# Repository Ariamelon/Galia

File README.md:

# Galia
USB-C breakout board.

## Disclaimer
This board is licensed under CC BY 4.0.
## Key Features
* Full ESD protection for data lines and VBUS.
* Two buttons on board that can be snapped off.
* Two M3 mounting holes, one of which is connected to ground for earthing the chassis.
* 6-pin JST SH connector capable of handling up to 3A power.

## Changelog
* 26/07/2023: Fixed position of button and mounting holes. Added JLC tooling holes.
* 25/07/2023: Changed 8 pin JST SH connector to 6 pin. Changed orientation of SH connectors for easier routing of wires. Added Ariamelon logo. Added PCB cutouts to allow for buttons to be snapped off.
* 21/07/2023: Changed 20 pin FFC to 7 pin and 8 pin JST SH connector. Fixed orientation.
* 18/07/2023: Changed JST connector back to 20 pin FFC. Centered connector.
* 17/07/2023: Changed 20 pin FFC connector to 14 pin JST SH connector. Repositioned components.
* 16/07/2023: Changed PTS645 LCSC part number.
* 14/07/2023: Initial public upload of V1.0.

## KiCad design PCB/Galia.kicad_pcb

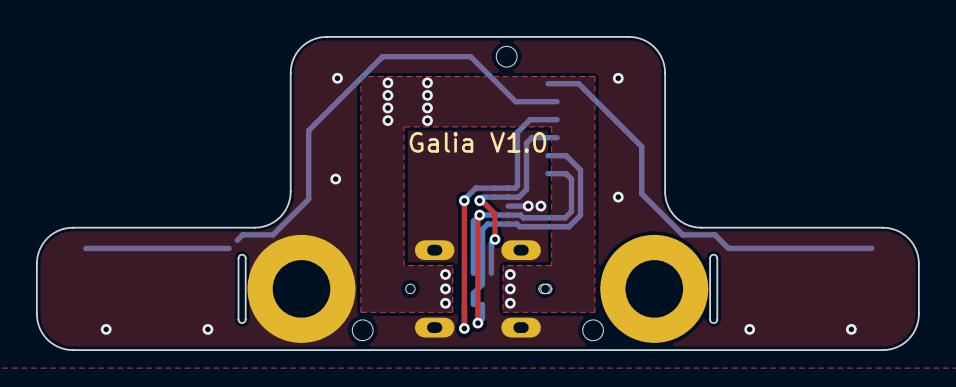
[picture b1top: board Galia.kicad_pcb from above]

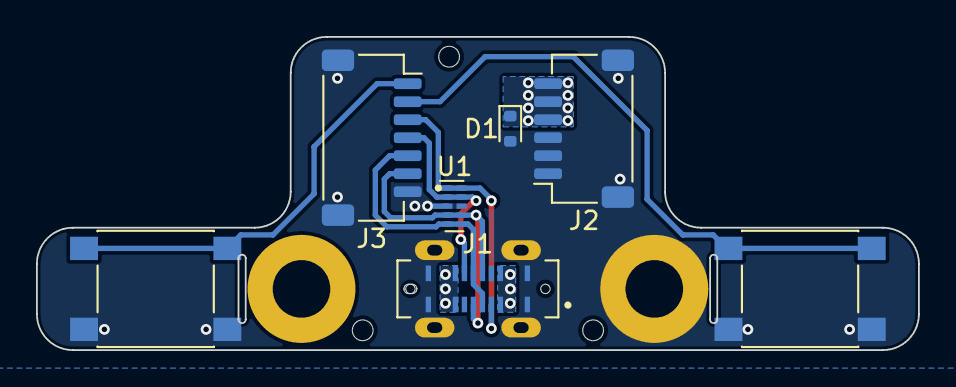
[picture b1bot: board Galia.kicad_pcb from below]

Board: 2 copper layers, 49.0 x 17.4 mm, 13 parts (9 on the bottom side), 8 nets.

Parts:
A1: Ariamelon Logo; Ariamelon_Logo_Mask
D1: 5V; D_SOD-523
H1, H2: M3; MountingHole_3.2mm_M3_Pad
H3, H4, H5: Tooling Hole; JLC Tooling Hole
J1: USB In; CON-USB4120-03-C-REVA
J2: Power; JST_SH_SM06B-SRSS-TB_1x06-1MP_P1.00mm_Horizontal
J3: I/O; JST_SH_SM07B-SRSS-TB_1x07-1MP_P1.00mm_Horizontal
SW1, SW2: PTS645; SW_SPST_PTS645
U1: TPD4E05U06; USON-10_2.5x1.0mm_P0.5mm

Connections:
/BOOTSEL: J3.1, SW2.2 (B)
/D+: J1.A6 (D+), J1.B6 (D+), J3.5, U1.5 (IO4), U1.6 (NC)
/D-: J1.A7 (D-), J1.B7 (D-), J3.6, U1.4 (IO3), U1.7 (NC)
/~RST: J3.2, SW1.2 (B)
CC1: J1.A5 (CC1), J3.3, U1.1 (IO1), U1.10 (NC)
CC2: J1.B5 (CC2), J3.4, U1.2 (IO2), U1.9 (NC)
GND: D1.2 (A), H2.1, J1.A1 (GND), J1.A12 (GND), J1.B1 (GND), J1.B12 (GND), J1.S1 (SHIELD), J2.1, J2.2, J2.3, J2.MP (MountPin), J3.7, J3.MP (MountPin), SW1.1 (A), SW2.1 (A), U1.3 (GND), U1.8 (GND)
VBUS: D1.1 (K), J1.A4 (VBUS), J1.A9 (VBUS), J1.B4 (VBUS), J1.B9 (VBUS), J2.4, J2.5, J2.6

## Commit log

2023-07-14 Changed PTS645 LCSC part number
2023-07-17 17/07/2023 update
    Changed 20 pin FFC connector to 14 pin JST SH connector. Repositioned components.
2023-07-18 18/07/2023 update.
    Changed JST connector back to 20 pin FFC. Centered connector.
2023-07-18 Added LCSC part number.
2023-07-21 21/07/2023 update.
    Changed 20 pin FFC to 7 pin and 8 pin JST SH connector. Fixed orientation.
2023-07-25 25/07/2023 update
    Changed 8 pin JST SH connector to 6 pin. Changed orientation of SH connectors for easier routing of wires. Added Ariamelon logo. Added PCB cutouts to allow for buttons to be snapped off.
2023-07-26 26/07/2023 update
    Fixed position of button and mounting holes. Added JLC tooling holes.
